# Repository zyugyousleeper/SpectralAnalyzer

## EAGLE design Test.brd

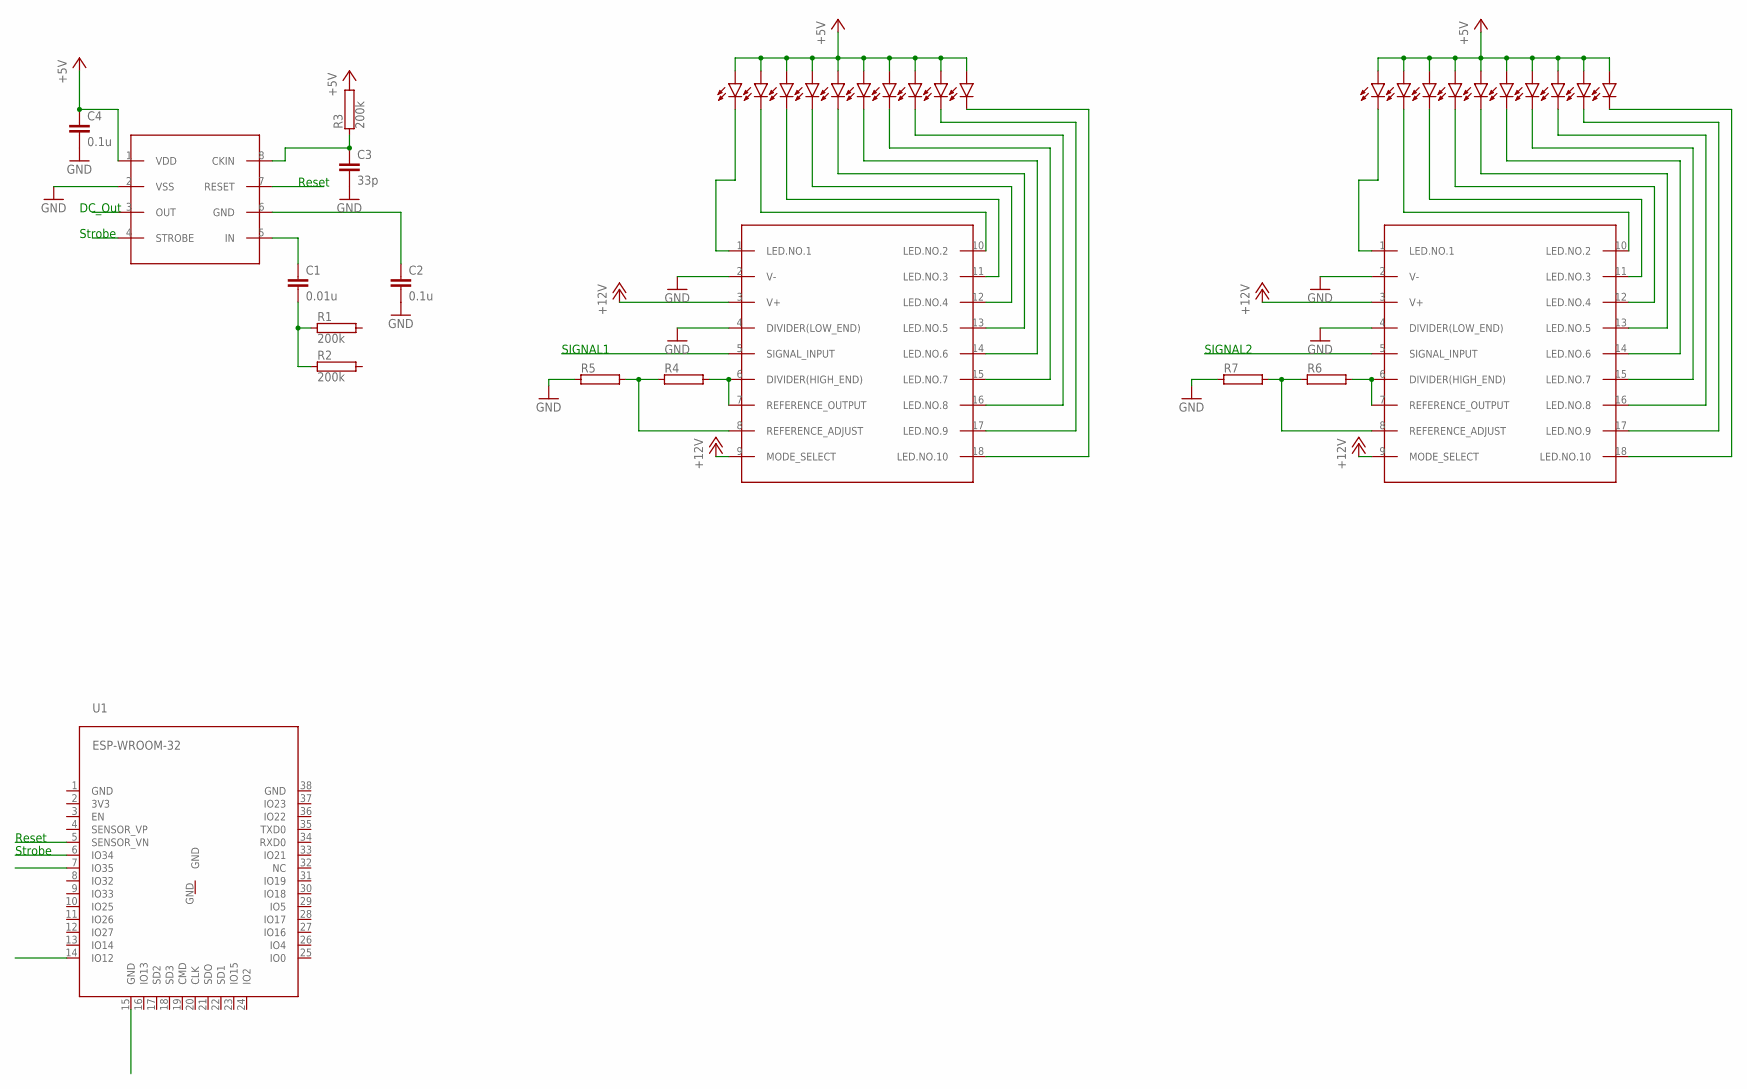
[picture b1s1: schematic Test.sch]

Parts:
C1: 0.01u; C2.5-2
C2, C4: 0.1u; C2.5-2
C3: 33p; C2.5-2
R1, R2, R3: 200k; AC01
R4, R5, R6, R7: RAC01; AC01
U1: ESP-WROOM-32
U$1: MSGEQ7; DIL08
U$2, U$4: LB10
U$3, U$5: LM3914; DIL18

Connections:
+5V: C4.1, R3.2, U$1.1 (VDD), U$2.1 (A), U$2.2 (A1), U$2.3 (A2), U$2.4 (A3), U$2.5 (A4), U$2.6 (A5), U$2.7 (A6), U$2.8 (A7), U$2.9 (A8), U$2.10 (A9), U$4.1 (A), U$4.2 (A1), U$4.3 (A2), U$4.4 (A3), U$4.5 (A4), U$4.6 (A5), U$4.7 (A6), U$4.8 (A7), U$4.9 (A8), U$4.10 (A9)
+12V: U$3.3 (V+), U$3.9 (MODE_SELECT), U$5.3 (V+), U$5.9 (MODE_SELECT)
GND: C2.2, C3.2, C4.2, R5.1, R7.1, U$1.2 (VSS), U$3.2 (V-), U$3.4 (DIVIDER(LOW_END)), U$5.2 (V-), U$5.4 (DIVIDER(LOW_END))
unnamed: C2.1, U$1.6 (GND)
unnamed: C3.1, R3.1, U$1.8 (CKIN)
unnamed: C1.2, R1.1, R2.1
unnamed: C1.1, U$1.5 (IN)
unnamed: U$2.11 (C), U$3.1 (LED.NO.1)
unnamed: U$2.12 (C1), U$3.10 (LED.NO.2)
unnamed: U$2.13 (C2), U$3.11 (LED.NO.3)
unnamed: U$2.14 (C3), U$3.12 (LED.NO.4)
unnamed: U$2.15 (C4), U$3.13 (LED.NO.5)
unnamed: U$2.16 (C5), U$3.14 (LED.NO.6)
unnamed: U$2.17 (C6), U$3.15 (LED.NO.7)
unnamed: U$2.18 (C7), U$3.16 (LED.NO.8)
unnamed: U$2.19 (C8), U$3.17 (LED.NO.9)
unnamed: U$2.20 (C9), U$3.18 (LED.NO.10)
unnamed: R4.1, R5.2, U$3.8 (REFERENCE_ADJUST)
unnamed: U$4.11 (C), U$5.1 (LED.NO.1)
unnamed: R4.2, U$3.6 (DIVIDER(HIGH_END)), U$3.7 (REFERENCE_OUTPUT)
unnamed: U$4.12 (C1), U$5.10 (LED.NO.2)
unnamed: U$4.13 (C2), U$5.11 (LED.NO.3)
unnamed: U$4.14 (C3), U$5.12 (LED.NO.4)
unnamed: U$4.15 (C4), U$5.13 (LED.NO.5)
unnamed: U$4.16 (C5), U$5.14 (LED.NO.6)
unnamed: U$4.17 (C6), U$5.15 (LED.NO.7)
unnamed: U$4.18 (C7), U$5.16 (LED.NO.8)
unnamed: U$4.19 (C8), U$5.17 (LED.NO.9)
unnamed: U$4.20 (C9), U$5.18 (LED.NO.10)
unnamed: R6.2, U$5.6 (DIVIDER(HIGH_END)), U$5.7 (REFERENCE_OUTPUT)
unnamed: R6.1, R7.2, U$5.8 (REFERENCE_ADJUST)

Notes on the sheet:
Strobe
Reset
DC_Out
SIGNAL1
SIGNAL2

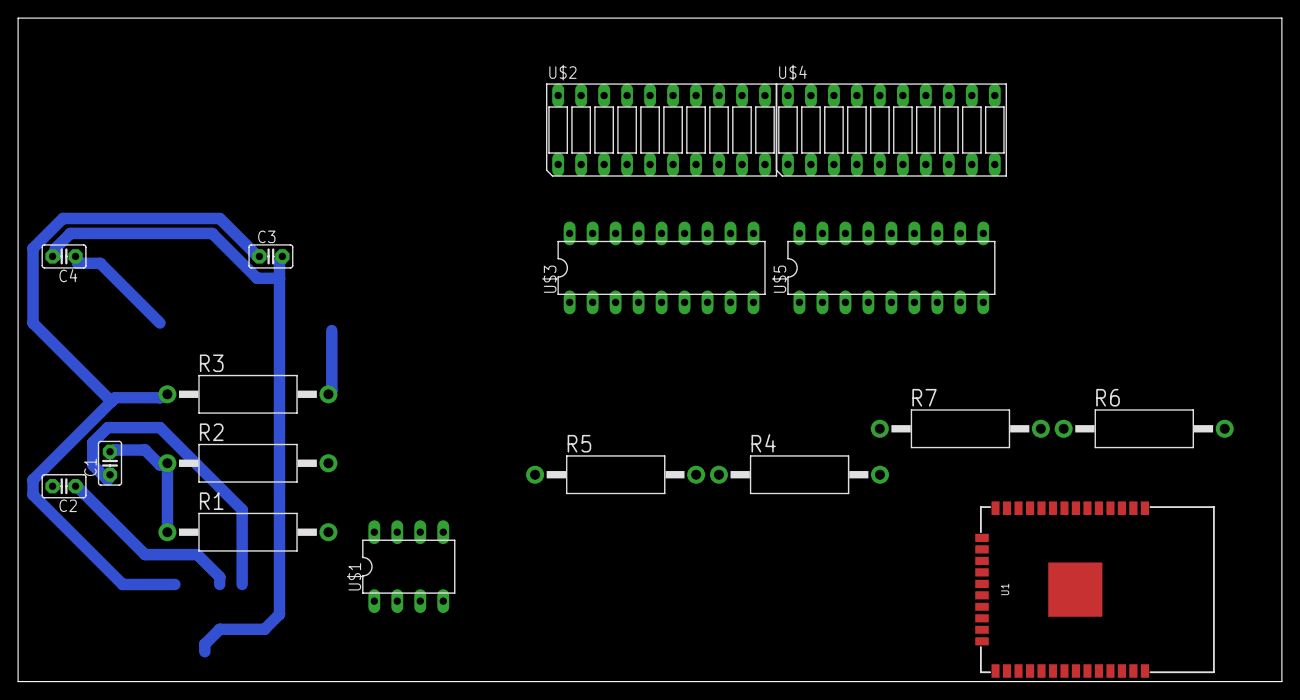
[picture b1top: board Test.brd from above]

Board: 2 copper layers, 139.7 x 73.3 mm, 17 parts (0 on the bottom side), 31 nets.

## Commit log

2018-12-11 [add]libraryを追加
2018-12-11 [add]回路図を追加
2018-12-14 [add]Test.sch
2018-12-19 [add]submodule
2018-12-19 [add]とりあえず書いてみた
2018-12-19 [fix]submoduleができていなかった
2018-12-19 [add]基板作成
2018-12-29 [fix]LEDsをいい感じにいい感じにした
2018-12-29 [fix]死んだライブラリをつかわない
2018-12-29 [rm]gitmoduels
2018-12-29 [add]gitignore
2018-12-29 [rm]はぁ
2018-12-29 [rm]libraryディレクトリを消去
2018-12-29 [mv]名前を変えた
2019-01-13 [add]値
2019-01-13 [add]LM3914
2019-01-13 [add]LM3914にこめ
2019-01-13 [add]esp32
2019-01-13 [fix]手直し
2019-02-17 [add]Nixie.schを追加
2019-02-17 [rm]いらないものを消去
2019-02-17 [mv]リネーム
2019-02-18 [rm]いったん全部消去
2019-02-18 [add]すべてを実装しなおした
2019-02-18 [fix]重大な欠陥
2019-02-18 [add]書き忘れ
2019-02-19 [add]pdfを生成
2019-02-20 [add]電源の追加
